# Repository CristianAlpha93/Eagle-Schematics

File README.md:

# Eagle-Schematics
Schematics and PCB layouts made with Eagle

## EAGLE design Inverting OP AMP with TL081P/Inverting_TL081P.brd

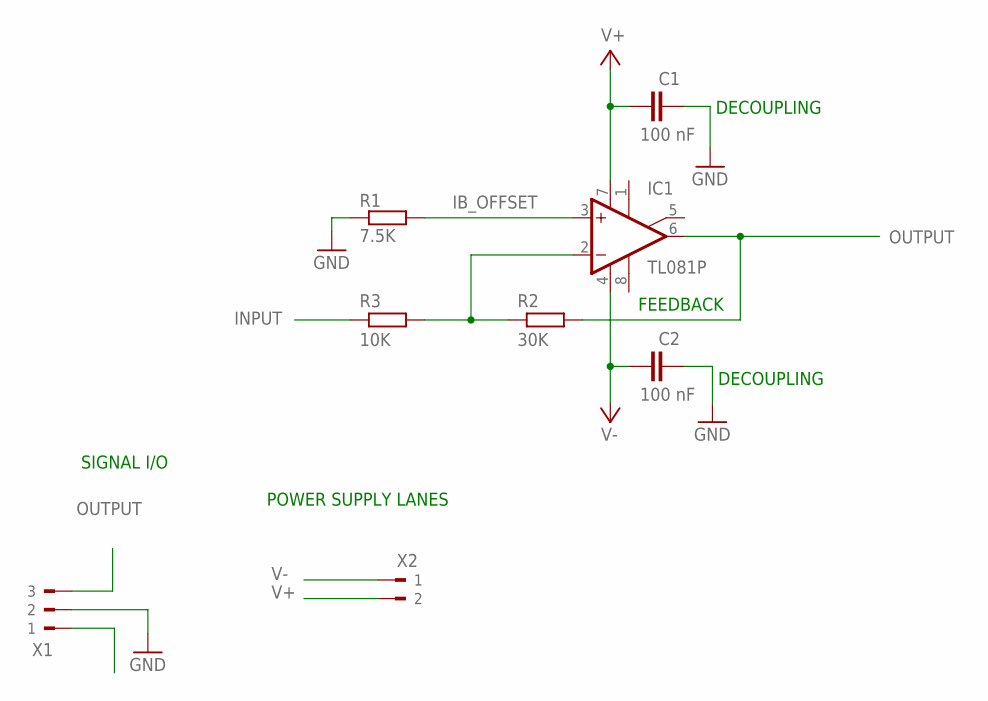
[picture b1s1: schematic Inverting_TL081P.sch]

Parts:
C1, C2: 100 nF; C025-025X050
IC1: TL081P; DIL08
R1: 7.5K; 0207/10
R2: 30K; 0207/10
R3: 10K; 0207/10
X1: 90-3
X2: 90-2

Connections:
GND: C1.1, C2.1, R1.1, X1.2
IB_OFFSET: IC1.3 (+IN), R1.2
INPUT: R3.1, X1.1
OP_AMP_INPUT: IC1.2 (-IN), R2.1, R3.2
OUTPUT: IC1.6 (OUT), R2.2, X1.3
V+: C1.2, IC1.7 (V+), X2.2
V-: C2.2, IC1.4 (V-), X2.1

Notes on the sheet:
DECOUPLING
POWER SUPPLY LANES
FEEDBACK
SIGNAL I/O

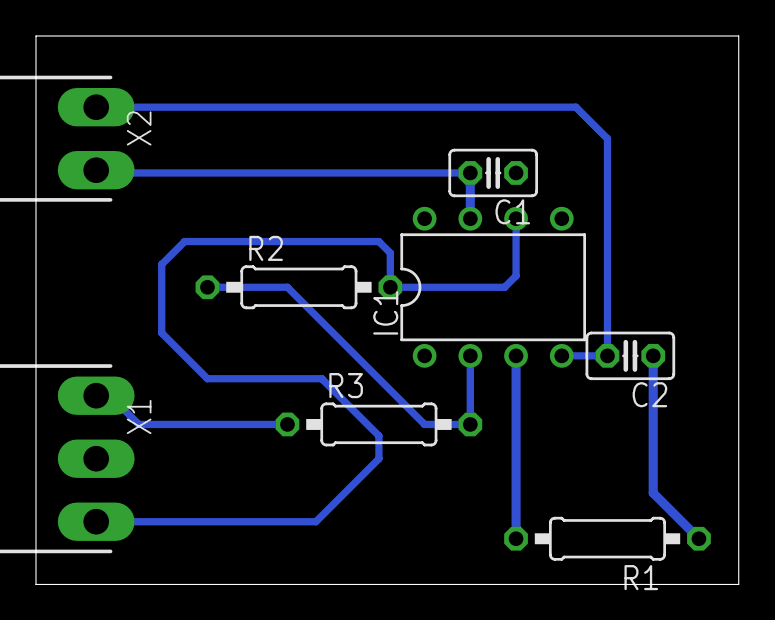
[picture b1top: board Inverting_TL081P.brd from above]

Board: 2 copper layers, 39.0 x 30.5 mm, 8 parts (0 on the bottom side), 7 nets.

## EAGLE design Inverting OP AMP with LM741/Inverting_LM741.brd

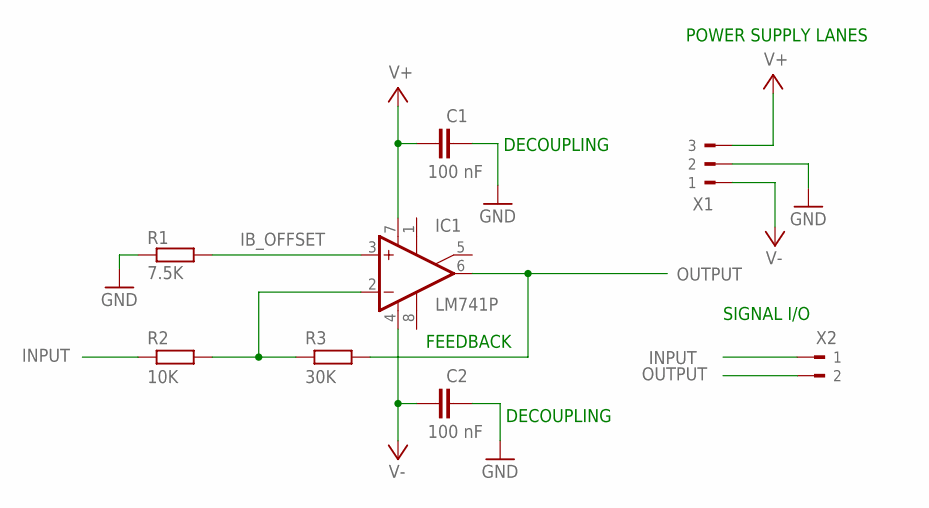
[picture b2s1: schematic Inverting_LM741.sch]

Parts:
C1, C2: 100 nF; C025-025X050
IC1: LM741P; DIL08
R1: 7.5K; 0207/10
R2: 10K; 0207/10
R3: 30K; 0207/10
X1: 90-3
X2: 90-2

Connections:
GND: C1.1, C2.1, R1.1, X1.2
IB_OFFSET: IC1.3 (+IN), R1.2
INPUT: R2.1, X2.1
OP_AMP_INPUT: IC1.2 (-IN), R2.2, R3.1
OUTPUT: IC1.6 (OUT), R3.2, X2.2
V+: C1.2, IC1.7 (V+), X1.3
V-: C2.2, IC1.4 (V-), X1.1

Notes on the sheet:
DECOUPLING
POWER SUPPLY LANES
FEEDBACK
SIGNAL I/O

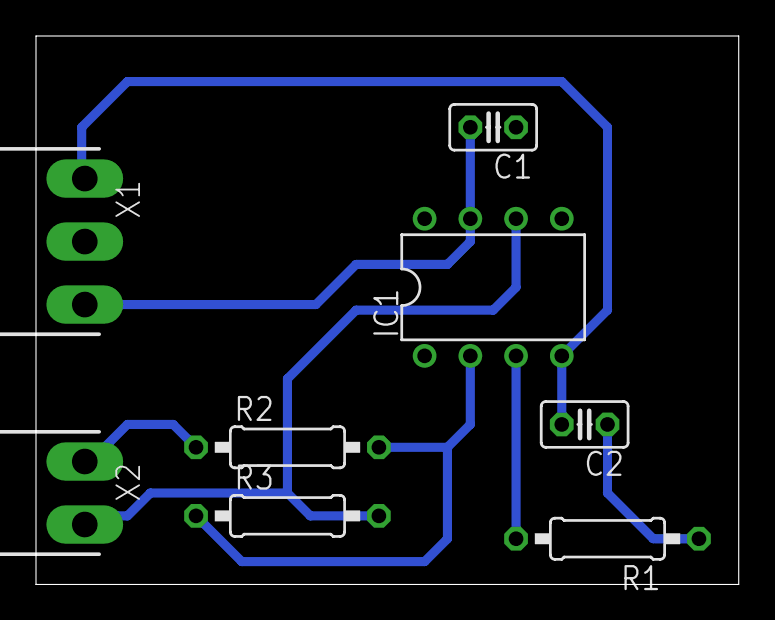
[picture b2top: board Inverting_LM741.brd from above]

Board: 2 copper layers, 39.0 x 30.5 mm, 8 parts (0 on the bottom side), 7 nets.

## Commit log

2017-01-27 LM741 - Inverting configuration
    Inverting OP AMP using a LM741 with bias current compensation.
2017-01-30 TL081P Inverting OP AMP
